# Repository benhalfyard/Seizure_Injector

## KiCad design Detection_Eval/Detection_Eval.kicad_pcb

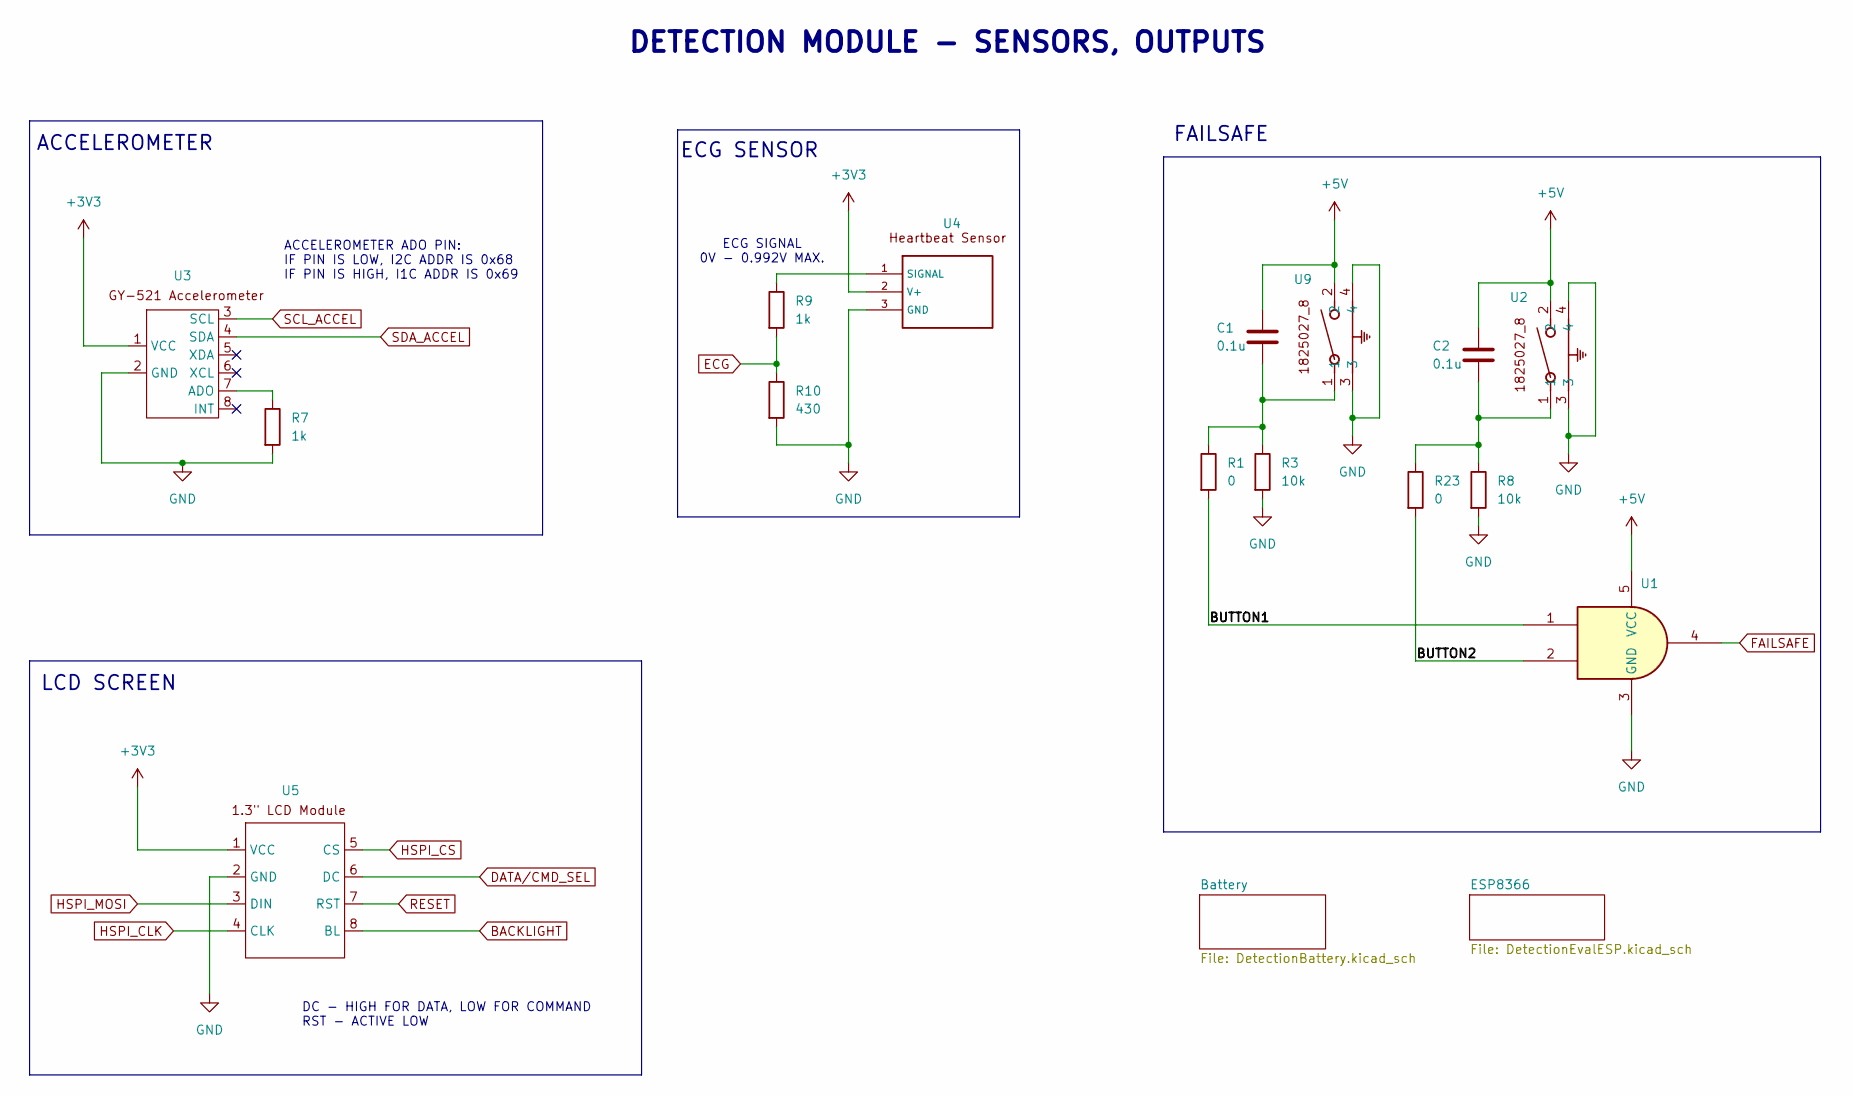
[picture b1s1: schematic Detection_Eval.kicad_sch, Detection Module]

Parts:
C1, C2: 0.1u; C_0603_1608Metric
R1, R23: 0; R_0402_1005Metric
R3, R8: 10k; R_0402_1005Metric
R7, R9: 1k; R_0402_1005Metric
R10: 430; R_0402_1005Metric
U1: SN74LVC1G08DCKR; SOT-353_SC-70-5_Handsoldering
U2, U9: SW2_1825027-C_TEC
U3: GY-521
U4: PinHeader_1x03_P2.54mm_Horizontal
U5: LCDSCREEN

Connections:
+3V3: U3.1 (VCC), U4.2 (V+), U5.1 (VCC); also elsewhere on the board
+5V: C1.1, C2.1, U1.5 (VCC), U2.2, U9.2; also elsewhere on the board
/BUTTON1: R1.2, U1.1
/BUTTON2: R23.2, U1.2
BACKLIGHT: U5.8 (BL); also elsewhere on the board
DATA/CMD_SEL: U5.6 (DC); also elsewhere on the board
ECG: R9.2, R10.1; also elsewhere on the board
FAILSAFE: U1.4; also elsewhere on the board
GND: R3.2, R7.2, R8.2, R10.2, U1.3 (GND), U2.3, U2.4, U3.2 (GND), U4.3 (GND), U5.2 (GND), U9.3, U9.4; also elsewhere on the board
HSPI_CLK: U5.4 (CLK); also elsewhere on the board
HSPI_CS: U5.5 (CS); also elsewhere on the board
HSPI_MOSI: U5.3 (DIN); also elsewhere on the board
unnamed: C1.2, R1.1, R3.1, U9.1
unnamed: C2.2, R8.1, R23.1, U2.1
unnamed: R7.1, U3.7 (ADO)
unnamed: R9.1, U4.1 (SIGNAL)
RESET: U5.7 (RST); also elsewhere on the board
SCL_ACCEL: U3.3 (SCL); also elsewhere on the board
SDA_ACCEL: U3.4 (SDA); also elsewhere on the board

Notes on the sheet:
ECG SIGNAL 0V - 0.992V MAX.
ACCELEROMETER ADO PIN: IF PIN IS LOW, I2C ADDR IS 0x68 IF PIN IS HIGH, I1C ADDR IS 0x69
ACCELEROMETER
DC - HIGH FOR DATA, LOW FOR COMMAND RST - ACTIVE LOW
ECG SENSOR
FAILSAFE
DETECTION MODULE - SENSORS, OUTPUTS
LCD SCREEN

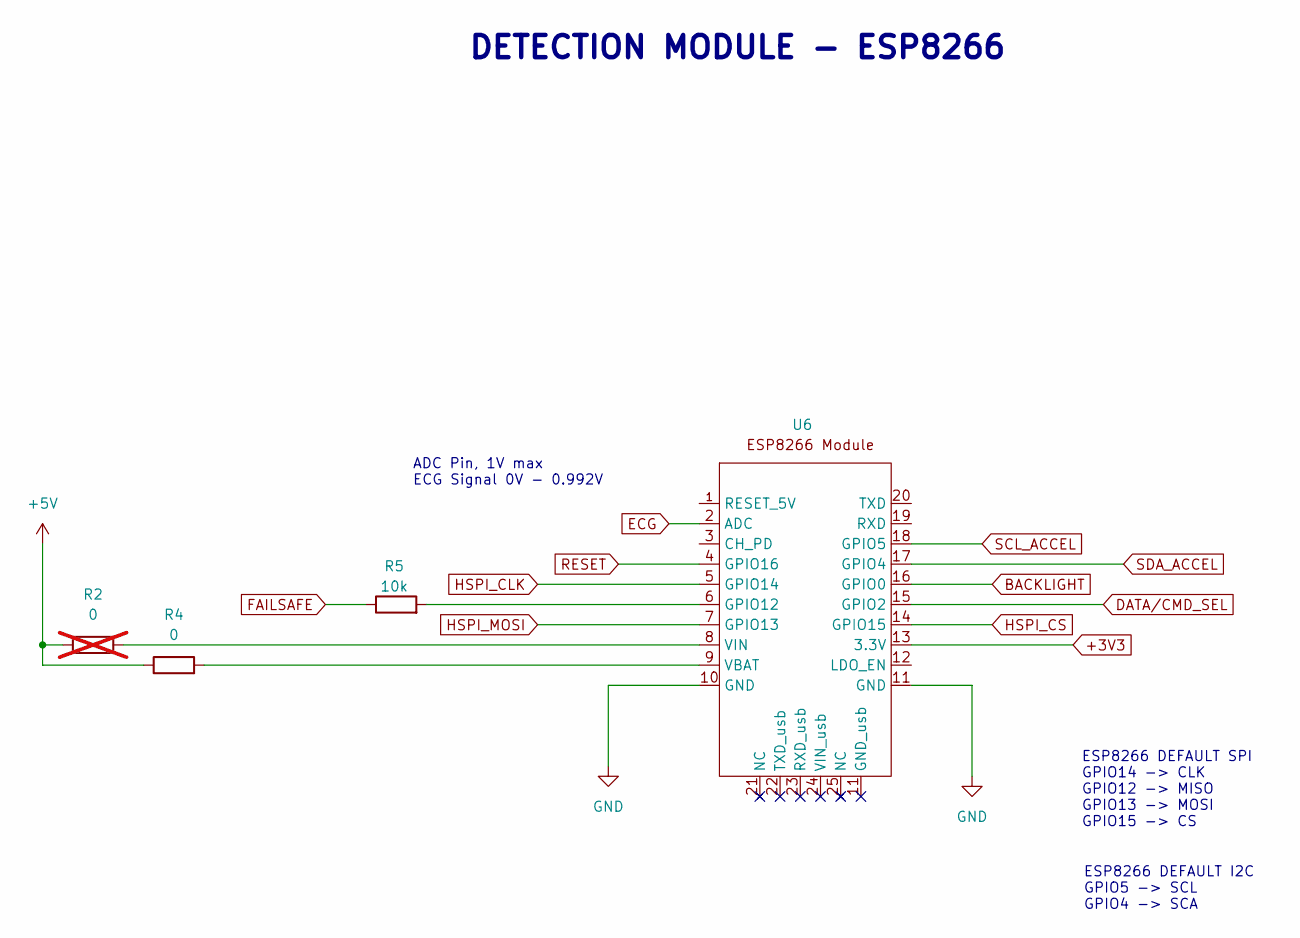
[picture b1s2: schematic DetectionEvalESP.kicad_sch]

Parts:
R2: 0; R_0402_1005Metric; not fitted
R4: 0; R_0402_1005Metric
R5: 10k; R_0402_1005Metric
U6: ESP8266; Adafruit_HUZZAH_ESP8266_breakout

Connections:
+3V3: U6.13 (3.3V); also elsewhere on the board
+5V: R2.1, R4.1; also elsewhere on the board
BACKLIGHT: U6.16 (GPIO0); also elsewhere on the board
DATA/CMD_SEL: U6.15 (GPIO2); also elsewhere on the board
ECG: U6.2 (ADC); also elsewhere on the board
FAILSAFE: R5.1; also elsewhere on the board
GND: U6.10 (GND), U6.11 (GND); also elsewhere on the board
HSPI_CLK: U6.5 (GPIO14); also elsewhere on the board
HSPI_CS: U6.14 (GPIO15); also elsewhere on the board
HSPI_MOSI: U6.7 (GPIO13); also elsewhere on the board
unnamed: R5.2, U6.6 (GPIO12)
unnamed: R4.2, U6.9 (VBAT)
unnamed: R2.2, U6.8 (VIN)
RESET: U6.4 (GPIO16); also elsewhere on the board
SCL_ACCEL: U6.18 (GPIO5); also elsewhere on the board
SDA_ACCEL: U6.17 (GPIO4); also elsewhere on the board

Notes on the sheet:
ADC Pin, 1V max ECG Signal 0V - 0.992V
ESP8266 DEFAULT SPI GPIO14 -> CLK GPIO12 -> MISO GPIO13 -> MOSI GPIO15 -> CS
DETECTION MODULE - ESP8266
ESP8266 DEFAULT I2C GPIO5 -> SCL GPIO4 -> SCA

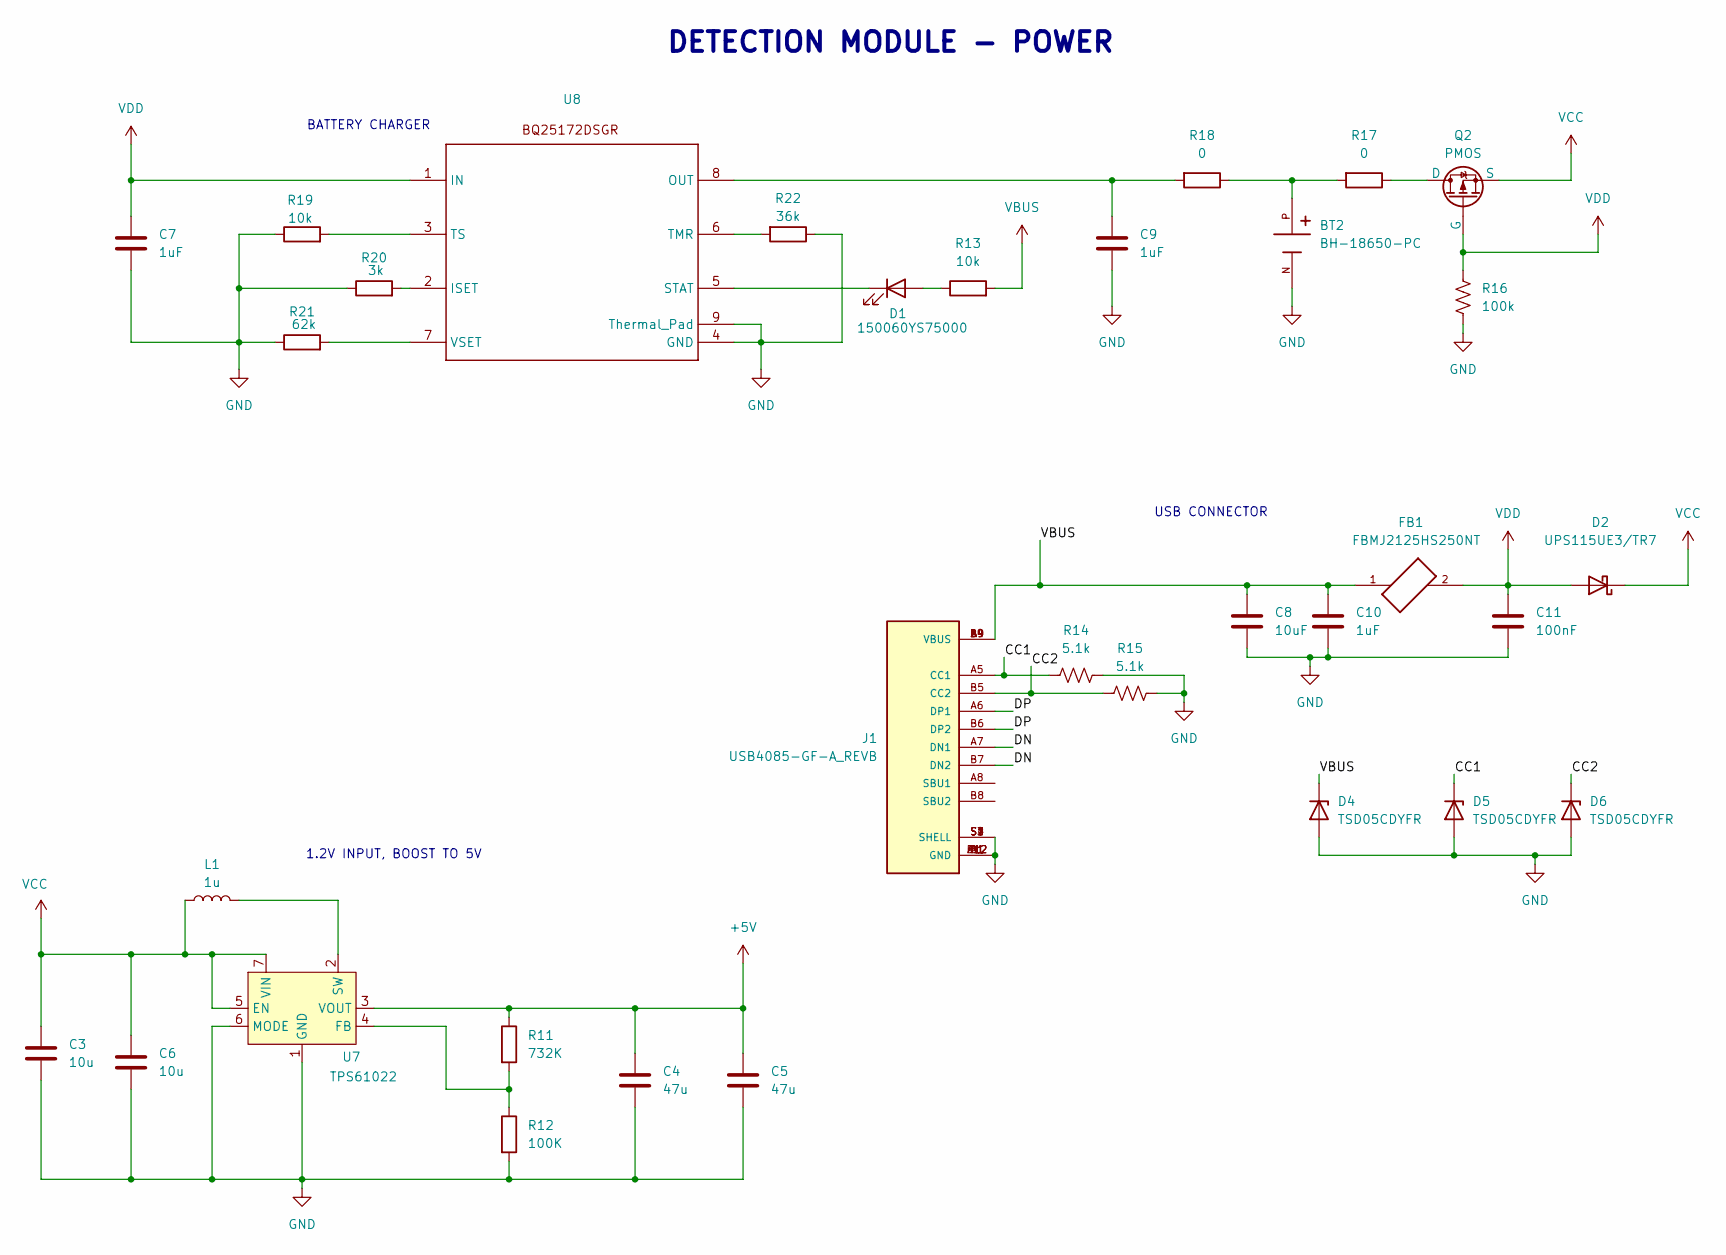
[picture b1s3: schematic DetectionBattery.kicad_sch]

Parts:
BT2: BH-18650-PC; BAT_BEAAAAPC; PARTREV 05/17/19
C3, C6: 10u; C_0603_1608Metric
C4, C5: 47u; C_0603_1608Metric
C7, C9, C10: 1uF; C_0603_1608Metric
C8: 10uF; C_0603_1608Metric
C11: 100nF; C_0603_1608Metric
D1: 150060YS75000; LED_0201_0603Metric_Pad0.64x0.40mm_HandSolder
D2: UPS115UE3/TR7; POWERMITE1_DO-216AA_MIS_MCH
D4, D5, D6: TSD05CDYFR; TVS_SOD2_DYF_TEX-L
FB1: FBMJ2125HS250NT; BEADC2012X105N
J1: USB4085-GF-A_REVB; GCT_USB4085-GF-A_REVB; PARTREV B; DigiKey_Part_Number 2073-USB4085-GF-ATR-ND
L1: 1u; IND_IHLP-2020CZ
Q2: PMOS; SOT65P210X110-3N
R11: 732K; R_0402_1005Metric
R12: 100K; R_0603_1608Metric
R13, R19: 10k; R_0402_1005Metric
R14, R15: 5.1k; R_0603_1608Metric
R16: 100k; R_0603_1608Metric
R17, R18: 0; R_0402_1005Metric
R20: 3k; R_0402_1005Metric
R21: 62k; R_0402_1005Metric
R22: 36k; R_0402_1005Metric
U7: TPS61022; Texas_RWU0007A_VQFN-7_2x2mm_P0.5mm
U8: BQ25172DSGR

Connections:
+5V: C4.1, C5.1, R11.1, U7.3 (VOUT); also elsewhere on the board
/Battery/CC1: D5.1 (K), J1.A5 (CC1), R14.1
/Battery/CC2: D6.1 (K), J1.B5 (CC2), R15.1
/Battery/DN: J1.A7 (DN1), J1.B7 (DN2)
/Battery/DP: J1.A6 (DP1), J1.B6 (DP2)
GND: BT2.N, C3.2, C4.2, C5.2, C6.2, C7.2, C8.2, C9.2, C10.2, C11.2, D4.2 (A), D5.2 (A), D6.2 (A), J1.A1 (GND), J1.A12 (GND), J1.B1 (GND), J1.B12 (GND), J1.S1 (SHELL), J1.S2 (SHELL), J1.S3 (SHELL), J1.S4 (SHELL), R12.2, R14.2, R15.2, R16.2, R19.1, R20.1, R21.1, R22.1, U7.1 (GND), U7.6 (MODE), U8.4 (GND), U8.9 (Thermal_Pad); also elsewhere on the board
unnamed: BT2.P, R17.2, R18.1
unnamed: D1.2 (A), R13.1
unnamed: D1.1 (K), U8.5 (STAT)
unnamed: Q2.1 (D), R17.1
unnamed: R11.2, R12.1, U7.4 (FB)
unnamed: L1.2, U7.2 (SW)
unnamed: R20.2, U8.2 (ISET)
unnamed: C9.1, R18.2, U8.8 (OUT)
unnamed: R22.2, U8.6 (TMR)
unnamed: R19.2, U8.3 (TS)
unnamed: R21.2, U8.7 (VSET)
VBUS: C8.1, C10.1, D4.1 (K), FB1.1, J1.A4 (VBUS), J1.A9 (VBUS), J1.B4 (VBUS), J1.B9 (VBUS), R13.2
VCC: C3.1, C6.1, D2.1 (K), L1.1, Q2.3 (S), U7.5 (EN), U7.7 (VIN)
VDD: C7.1, C11.1, D2.2 (A), FB1.2, Q2.2 (G), R16.1, U8.1 (IN)

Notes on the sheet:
BATTERY CHARGER
USB CONNECTOR
DETECTION MODULE - POWER
1.2V INPUT, BOOST TO 5V

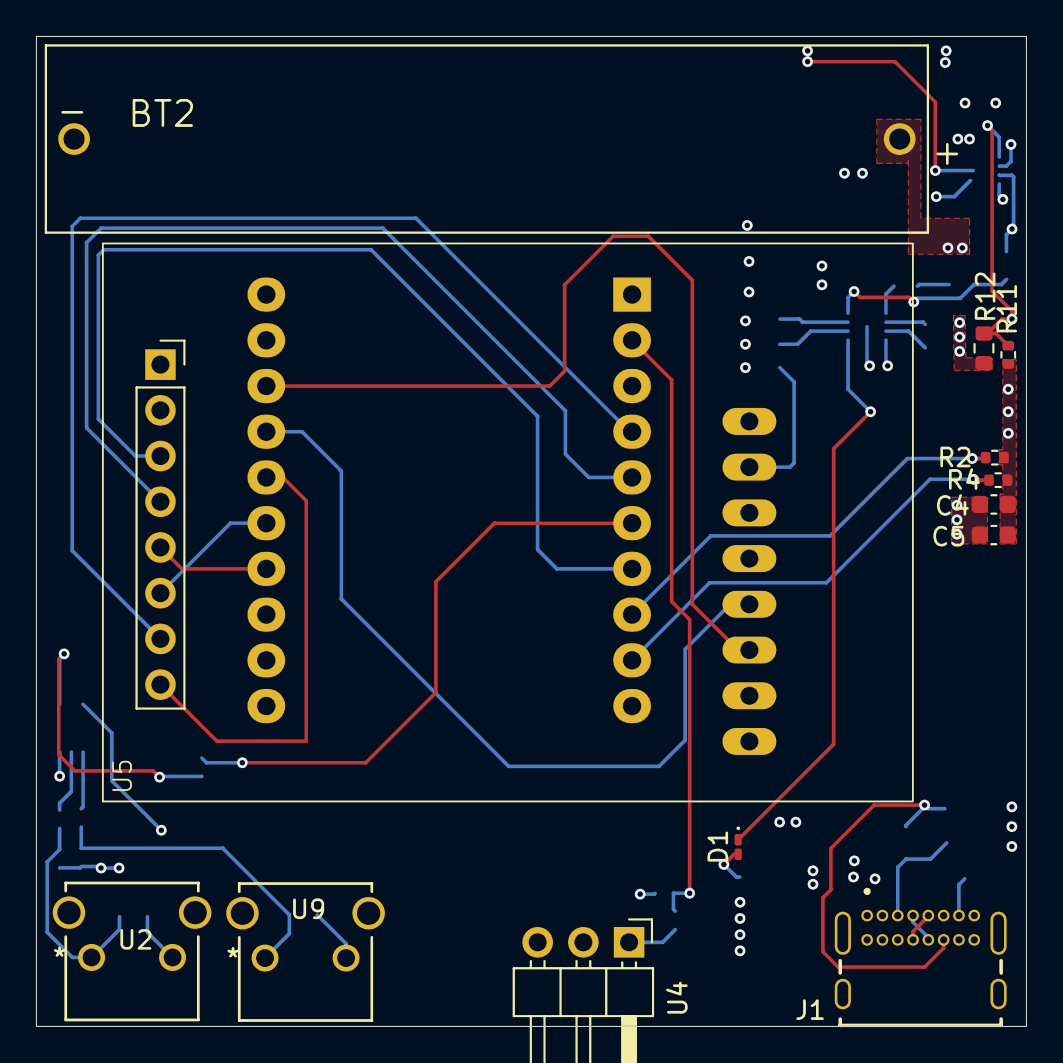
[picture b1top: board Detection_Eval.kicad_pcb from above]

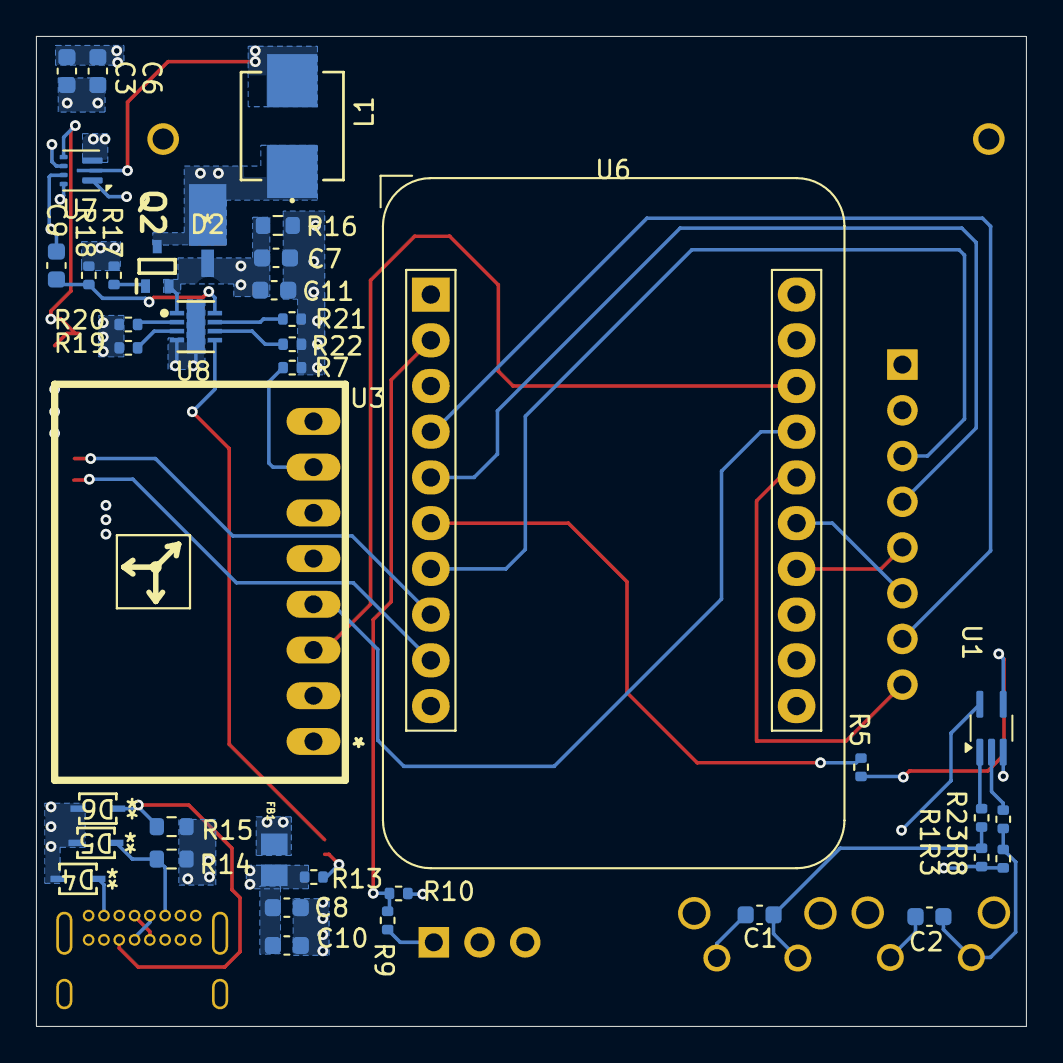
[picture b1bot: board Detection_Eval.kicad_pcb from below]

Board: 4 copper layers, 55.0 x 55.0 mm, 52 parts (39 on the bottom side), 40 nets.

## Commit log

2025-01-14 Created Detection Kicad Proj
2025-01-15 Created and Placed ESP Symbol
2025-01-15 added accelerometer symbol
2025-01-16 madison test
2025-01-16 Madison_01-16
    Updated ESP, MP3 symbols
    Added speaker and USB connection
2025-01-17 Madison_01-16pt2
    Added LED, Button and accelerometer circuit
    Updated accelerometer symbol
    Updated title block
2025-01-20 Madison_01-20
    Adding footprints 1
2025-01-20 Madison_01-20_2
    Updated further footprints
2025-01-21 Madison_01-21
    Further sch updates based on review
2025-02-03 Madison_02-03_REV002
    this is the begining of REV002
    Added LCD, heartbeat monitor
    Added page for ESP8266 and USB
    Added AND failsafe circuit
    Further page organization
    NEEDS REVIEW
2025-02-05 Madison_02-04
    Battery added
2025-02-05 Madison_02-05
    1.2V to 5V battery regulator added
    chose AAAA 600maH rechargeable battery
2025-02-05 Madison_02-05_2
    Added battery charger circuit
    Added footprints to accelerometer, lcd screen, buttons, AND gate, batt charger, batt holder
2025-02-06 Madison_02-06
    final footprints added and layout positioning mostly done
2025-02-07 LAYOUT DONE
2025-02-07 GERBER FILES
